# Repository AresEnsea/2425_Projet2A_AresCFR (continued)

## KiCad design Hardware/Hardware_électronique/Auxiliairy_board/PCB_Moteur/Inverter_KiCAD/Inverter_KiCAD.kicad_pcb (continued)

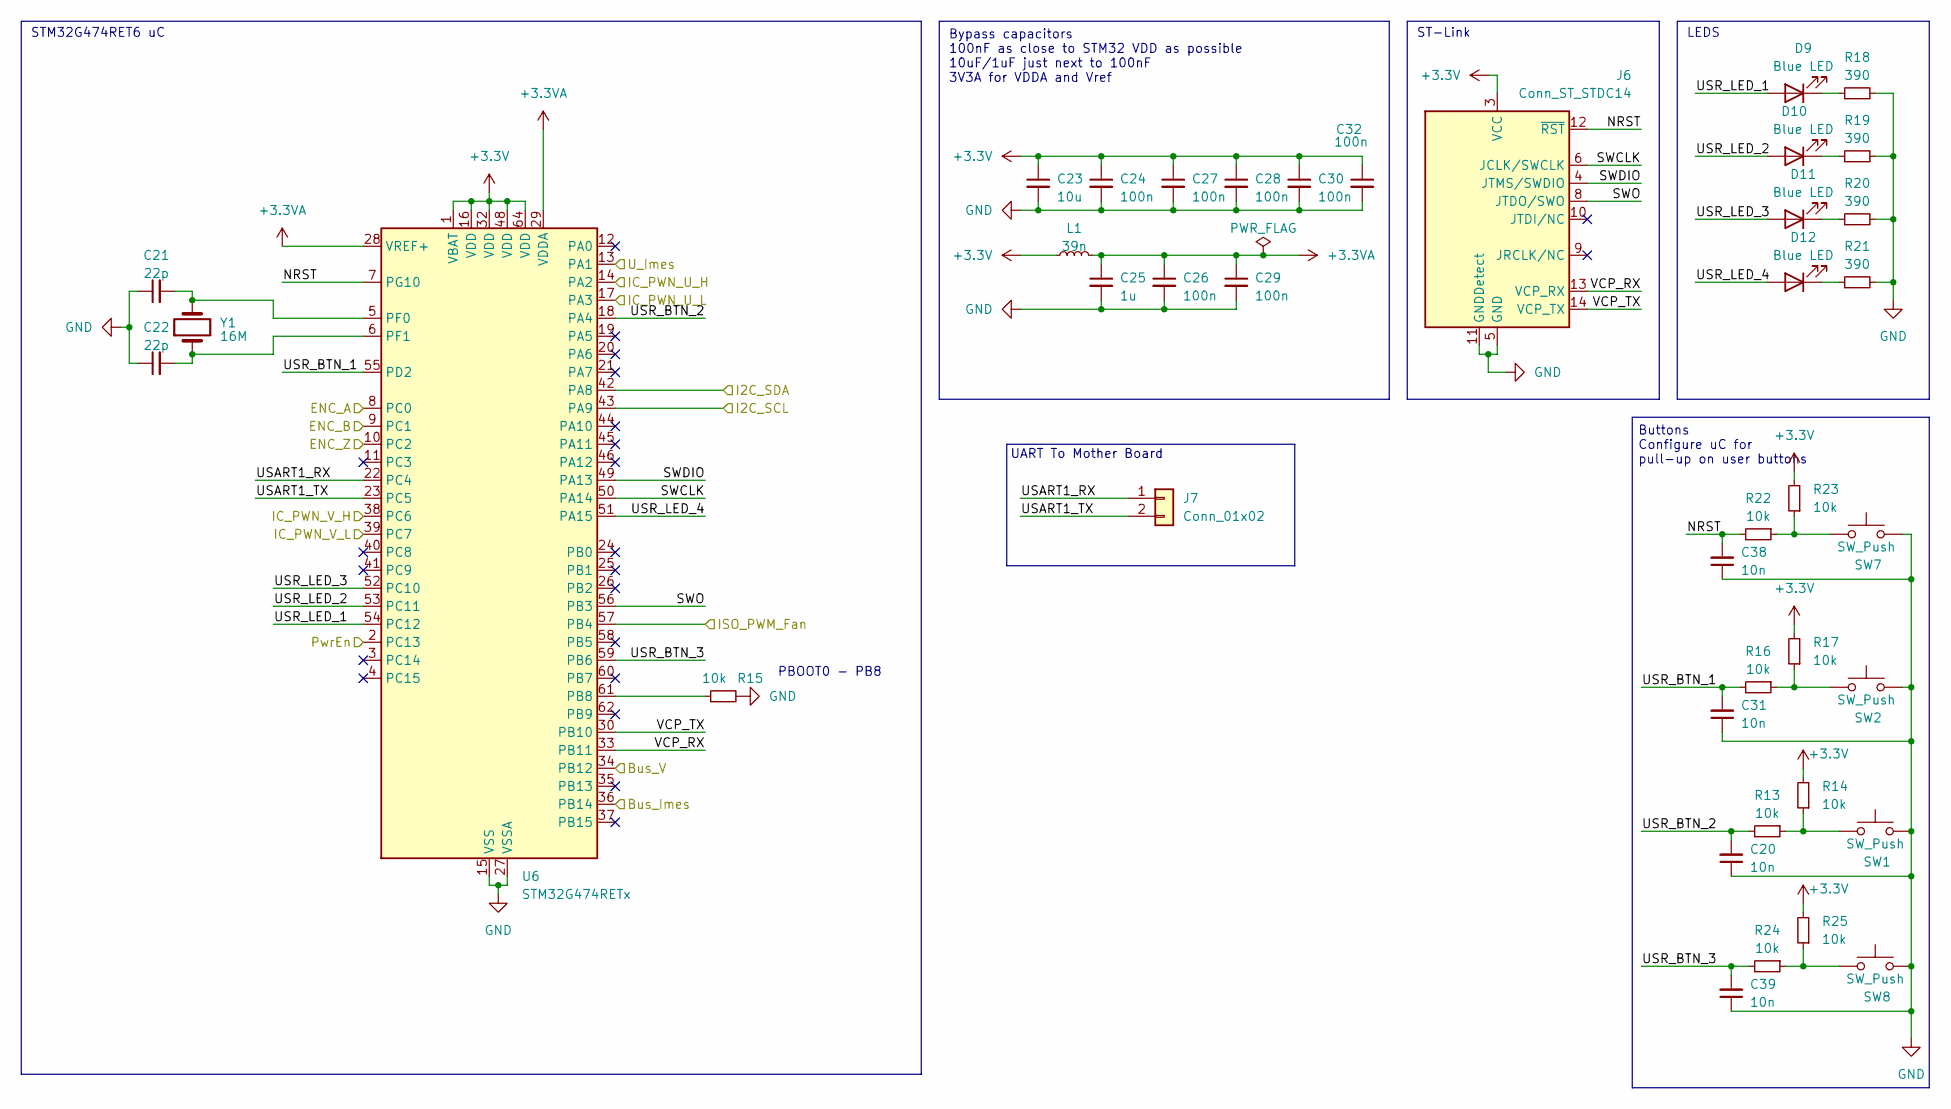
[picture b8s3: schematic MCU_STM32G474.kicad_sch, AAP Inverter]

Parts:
C20, C31, C38, C39: 10n; C_0402_1005Metric
C21, C22: 22p; C_0402_1005Metric
C23: 10u; C_0603_1608Metric_Pad1.08x0.95mm_HandSolder
C24, C26, C27, C28, C29, C30, C32: 100n; C_0402_1005Metric
C25: 1u; C_0603_1608Metric_Pad1.08x0.95mm_HandSolder
D9, D10, D11, D12: Blue LED; LED_0603_1608Metric
J6: Conn_ST_STDC14; PinHeader_2x07_P1.27mm_Vertical_SMD
J7: Conn_01x02; JST_XH_B2B-XH-A_1x02_P2.50mm_Vertical
L1: 39n; L_0603_1608Metric
R13, R14, R15, R16, R17, R22, R23, R24, R25: 10k; R_0402_1005Metric
R18, R19, R20, R21: 390; R_0402_1005Metric
SW1, SW2, SW7, SW8: SW_Push; 435451019820
U6: STM32G474RETx; LQFP-64_10x10mm_P0.5mm
Y1: 16M; ABLS-7.3728MHZ-CL-RESR-A-1-G-F

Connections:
+3.3V: C23.1, C24.1, C27.1, C28.1, C30.1, C32.1, J6.3 (VCC), L1.1, R14.2, R17.2, R23.2, R25.2, U6.1 (VBAT), U6.16 (VDD), U6.32 (VDD), U6.48 (VDD), U6.64 (VDD); also elsewhere on the board
+3.3VA: C25.1, C26.1, C29.1, L1.2, U6.28 (VREF+), U6.29 (VDDA)
/ENC_A: U6.8 (PC0); also elsewhere on the board
/ENC_B: U6.9 (PC1); also elsewhere on the board
/ENC_C: U6.10 (PC2); also elsewhere on the board
/I2C_SCL: U6.43 (PA9); also elsewhere on the board
/I2C_SDA: U6.42 (PA8); also elsewhere on the board
/Imes_mot: U6.13 (PA1); also elsewhere on the board
/Imes_vbus: U6.36 (PB14); also elsewhere on the board
/In_A_H: U6.14 (PA2); also elsewhere on the board
/In_A_L: U6.17 (PA3); also elsewhere on the board
/In_B_H: U6.38 (PC6); also elsewhere on the board
/In_B_L: U6.39 (PC7); also elsewhere on the board
/MCU_STM32G475/NRST: C38.2, J6.12 (~RST), R22.2, U6.7 (PG10)
/MCU_STM32G475/SWCLK: J6.6 (JCLK/SWCLK), U6.50 (PA14)
/MCU_STM32G475/SWDIO: J6.4 (JTMS/SWDIO), U6.49 (PA13)
/MCU_STM32G475/SWO: J6.8 (JTDO/SWO), U6.56 (PB3)
/MCU_STM32G475/USR_BTN_1: C31.2, R16.2, U6.55 (PD2)
/MCU_STM32G475/USR_BTN_2: C20.2, R13.2, U6.18 (PA4)
/MCU_STM32G475/USR_BTN_3: C39.2, R24.2, U6.59 (PB6)
/MCU_STM32G475/USR_LED_1: D9.2 (A), U6.54 (PC12)
/MCU_STM32G475/USR_LED_2: D10.2 (A), U6.53 (PC11)
/MCU_STM32G475/USR_LED_3: D11.2 (A), U6.52 (PC10)
/MCU_STM32G475/USR_LED_4: D12.2 (A), U6.51 (PA15)
/MCU_STM32G475/VCP_RX: J6.13 (VCP_RX), U6.33 (PB11)
/MCU_STM32G475/VCP_TX: J6.14 (VCP_TX), U6.30 (PB10)
/PWM_FAN: U6.57 (PB4); also elsewhere on the board
/Pwr_EN: U6.2 (PC13); also elsewhere on the board
/VBus_Sense: U6.34 (PB12); also elsewhere on the board
GND: C20.1, C21.1, C22.1, C23.2, C24.2, C25.2, C26.2, C27.2, C28.2, C29.2, C30.2, C31.1, C32.2, C38.1, C39.1, J6.5 (GND), J6.7 (GND), J6.11 (GNDDetect), J7.4, R15.2, R18.2, R19.2, R20.2, R21.2, SW1.2, SW2.2, SW7.2, SW8.2, U6.15 (VSS), U6.27 (VSSA), U6.31 (VSS), U6.47 (VSS), U6.63 (VSS); also elsewhere on the board
unnamed: D9.1 (K), R18.1
unnamed: D10.1 (K), R19.1
unnamed: D11.1 (K), R20.1
unnamed: D12.1 (K), R21.1
unnamed: R13.1, R14.1, SW1.1
unnamed: R16.1, R17.1, SW2.1
unnamed: R22.1, R23.1, SW7.1
unnamed: R24.1, R25.1, SW8.1
unnamed: R15.1, U6.61 (PB8)
unnamed: C21.2, U6.5 (PF0), Y1.2
unnamed: C22.2, U6.6 (PF1), Y1.1

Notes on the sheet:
ST-Link
Bypass capacitors 100nF as close to STM32 VDD as possible 10uF/1uF just next to 100nF 3V3A for VDDA and Vref
Buttons Configure uC for pull-up on user buttons
UART To Mother Board
PBOOT0 - PB8
STM32G474RET6 uC
LEDS

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
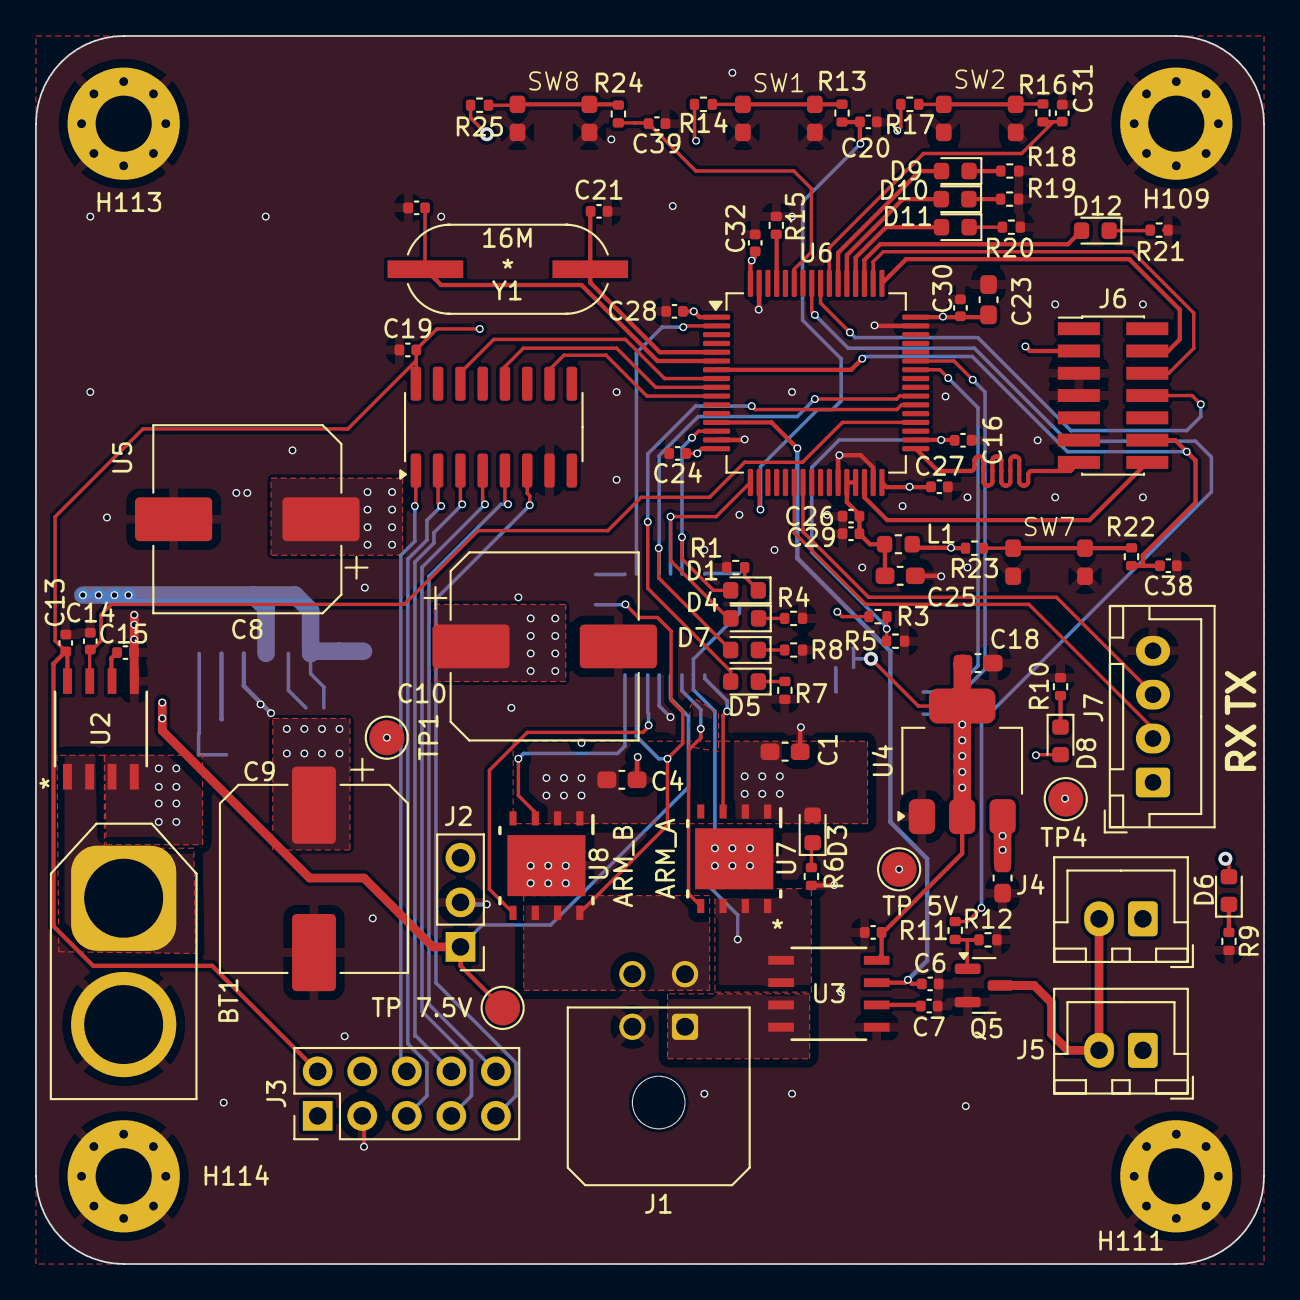
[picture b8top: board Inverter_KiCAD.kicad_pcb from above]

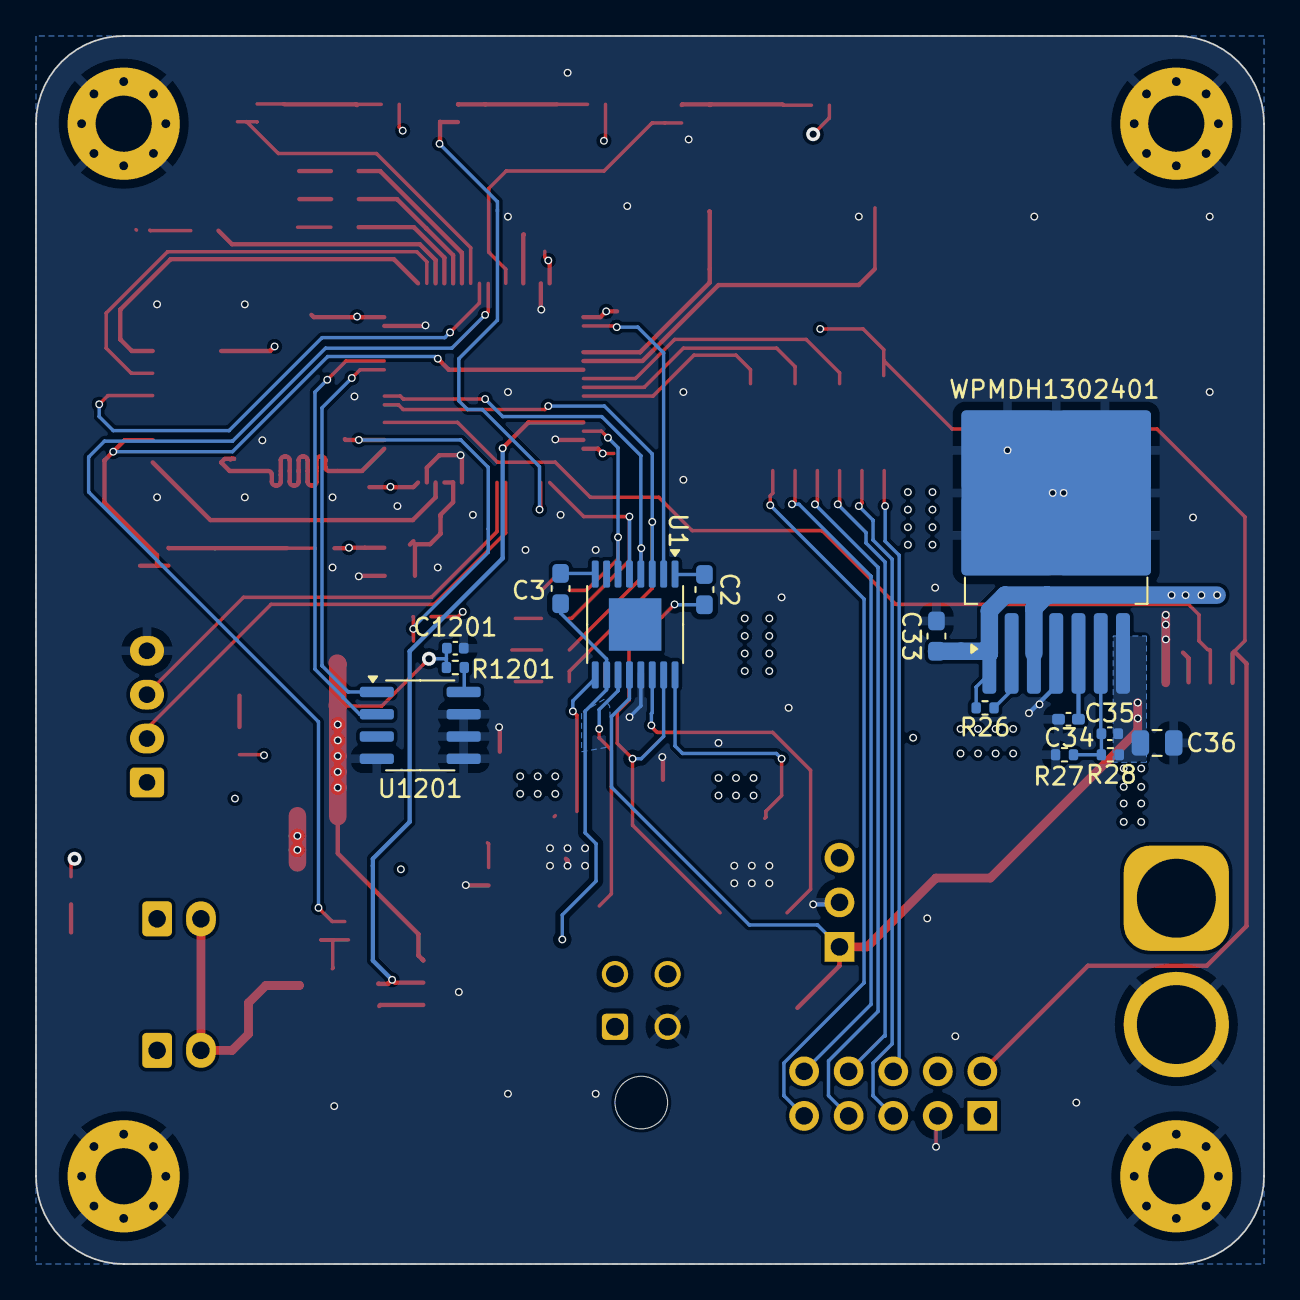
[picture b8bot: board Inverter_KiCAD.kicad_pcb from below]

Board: 4 copper layers, 70.0 x 70.0 mm, 109 parts (14 on the bottom side), 77 nets.

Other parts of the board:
TP 5V, TP 7.5V: TestPoint; TestPoint_Pad_D2.0mm
WPMDH1302401: TO-263-7_TabPin8

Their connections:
+5V: TP 5V.1; also elsewhere on the board
+7.5V: TP 7.5V.1, WPMDH1302401.7 (Vout); also elsewhere on the board
GND: WPMDH1302401.4 (AGND), WPMDH1302401.8 (PGND); also elsewhere on the board
unnamed 48: WPMDH1302401.6 (FB); also elsewhere on the board
unnamed 49: WPMDH1302401.2 (RON); also elsewhere on the board
unnamed 50: WPMDH1302401.5 (SS); also elsewhere on the board
VBUS: WPMDH1302401.1 (Vin), WPMDH1302401.3 (EN); also elsewhere on the board

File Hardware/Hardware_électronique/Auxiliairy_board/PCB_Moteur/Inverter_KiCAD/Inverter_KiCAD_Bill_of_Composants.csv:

Reference;Value;Datasheet;Footprint;Qty;Magasin
BT1;Battery;~;Connector_AMASS:AMASS_XT60-M_1x02_P7.20mm_Vertical;1;
C1,C4,C17,C23,C33;10u;-- valeurs mixtées --;Capacitor_SMD:C_0603_1608Metric_Pad1.08x0.95mm_HandSolder;5;
C2,C3,C25;1u;~;Capacitor_SMD:C_0603_1608Metric_Pad1.08x0.95mm_HandSolder;3;
C5,C6,C7,C13,C14,C15;4.7n;~;Capacitor_SMD:C_0402_1005Metric;6;
C8,C9,C10;220u;~;Capacitor_SMD:CP_Elec_10x10.5;3;
C16,C20,C31,C38,C39;10n;~;Capacitor_SMD:C_0402_1005Metric;5;
C18;22u;~;Capacitor_SMD:C_0603_1608Metric_Pad1.08x0.95mm_HandSolder;1;
C19,C24,C26,C27,C28,C29,C30,C32,C1201;100n;~;Capacitor_SMD:C_0402_1005Metric;9;
C21,C22;22p;~;Capacitor_SMD:C_0402_1005Metric;2;
C34;4.7nF;~;Capacitor_SMD:C_0402_1005Metric_Pad0.74x0.62mm_HandSolder;1;
C35;22nF;~;Capacitor_SMD:C_0402_1005Metric;1;
C36;47u;~;Capacitor_SMD:C_0805_2012Metric;1;
Converter_DCDC_WPMDH1302401;~;;Package_TO_SOT_SMD:TO-263-7_TabPin8;1;
D1,D3,D4,D5,D6,D7,D8;Red LED;~;LED_SMD:LED_0603_1608Metric;7;
D9,D10,D11,D12;Blue LED;~;LED_SMD:LED_0603_1608Metric;4;
H109,H111,H113,H114;MountingHole_Pad;~;MountingHole:MountingHole_3.2mm_M3_Pad_Via;4;
J1;Conn_02x02_Top_Bottom;~;Connector_Molex:Molex_Micro-Fit_3.0_43045-0400_2x02_P3.00mm_Horizontal;1;
J2;173010542;https://www.we-online.com/components/products/datasheet/1730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;Connector_PinHeader_2.54mm:PinHeader_1x03_P2.54mm_Vertical;1;
J3;Conn_02x05_Odd_Even;~;Connector_PinHeader_2.54mm:PinHeader_2x05_P2.54mm_Vertical;1;
J4,J5;Conn_01x02;~;Connector_JST:JST_XH_B2B-XH-A_1x02_P2.50mm_Vertical;2;
J6;Conn_ST_STDC14;https://www.st.com/content/ccc/resource/technical/document/u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;Connector_PinHeader_1.27mm:PinHeader_2x07_P1.27mm_Vertical_SMD;1;
J7;Conn_01x04_Pin;~;Connector_JST:JST_XH_B4B-XH-A_1x04_P2.50mm_Vertical;1;
L1;39n;~;Inductor_SMD:L_0603_1608Metric;1;
Q5;SQ2310ES;~;Package_TO_SOT_SMD:SOT-23;1;
R1,R4,R7,R8,R10,R18,R19,R20,R21;390;~;Resistor_SMD:R_0402_1005Metric;9;
R3;100k;~;Resistor_SMD:R_0402_1005Metric;1;
R5;8.2K;~;Resistor_SMD:R_0402_1005Metric;1;
R6;2k7;~;Resistor_SMD:R_0402_1005Metric;1;
R9;680;~;Resistor_SMD:R_0402_1005Metric;1;
R11;22;~;Resistor_SMD:R_0402_1005Metric;1;
R12,R13,R14,R15,R16,R17,R22,R23,R24,R25;10k;~;Resistor_SMD:R_0402_1005Metric;10;
R26;287k;~;Resistor_SMD:R_0402_1005Metric;1;
R27;1.91k;~;Resistor_SMD:R_0402_1005Metric;1;
R28;34k;~;Resistor_SMD:R_0402_1005Metric;1;
R1201;200;~;Resistor_SMD:R_0402_1005Metric;1;
SW1,SW2,SW7,SW8;SW_Push;~;Custom:435451019820;4;
TP1,TP2,TP3,TP4;TestPoint;~;TestPoint:TestPoint_Pad_D2.0mm;4;
U1;MIC4606;https://www.mouser.fr/datasheet/2/268/MIC4606_85V_Full_Bridg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;Package_SO:TSSOP-16-1EP_4.4x5mm_P0.65mm_EP3x3mm;1;
U2,U3;GO 10-SME/SP3;GO 10-SME;Custom:SOIC8-GO-SME&slash_SP3_LEM;2;
U4;AZ1117-3.3;https://www.diodes.com/assets/Datasheets/AZ1117.pdf;Package_TO_SOT_SMD:SOT-223-3_TabPin2;1;
U5;MAX3097ECSE+;https://www.mouser.fr/datasheet/2/609/MAX3097E_MAX3098E-3128450.pdf;Package_SO:SOIC-16_3.9x9.9mm_P1.27mm;1;
U6;STM32G474RETx;https://www.st.com/resource/en/datasheet/stm32g474re.pdf;Package_QFP:LQFP-64_10x10mm_P0.5mm;1;
U7,U8;CSD86350Q5D;CSD86350Q5D;CSD87351Q5D:DQY0008A;2;
U1201;TCN75A;https://docs.rs-online.com/fc92/0900766b80d0dfb5.pdf;Package_SO:SOIC-8_3.9x4.9mm_P1.27mm;1;
Y1;16M;https://4donline.ihs.com/images/VipMasterIC/IC/ABRC/ABRCS034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;Custom:ABLS-7.3728MHZ-CL-RESR-A-1-G-F;1;

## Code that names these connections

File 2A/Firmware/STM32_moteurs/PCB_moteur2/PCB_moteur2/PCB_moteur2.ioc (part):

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Mcu.Name=STM32G474R(B-C-E)Tx
Mcu.Package=LQFP64
Mcu.UserName=STM32G474RETx
PA1.Mode=IN2-Single-Ended
PA1.Signal=ADC1_IN2
PA13.Mode=Trace_Asynchronous_SW
PA13.Signal=SYS_JTMS-SWDIO
PA14.Mode=Trace_Asynchronous_SW
PA14.Signal=SYS_JTCK-SWCLK
PA15.GPIOParameters=GPIO_Label
PA15.GPIO_Label=USR_LED_4
PA15.Signal=GPIO_Output
PA2.Signal=S_TIM2_CH3
PA3.Signal=S_TIM2_CH4
PA4.GPIOParameters=GPIO_Label
PA4.GPIO_Label=USR_BTN_2
PA4.Signal=GPXTI4
PA8.Mode=I2C
PA8.Signal=I2C2_SDA
PA9.Mode=I2C
PA9.Signal=I2C2_SCL
PB10.GPIOParameters=GPIO_Label
PB10.GPIO_Label=VCP_TX
PB10.Mode=Asynchronous
PB10.Signal=USART3_TX
PB11.GPIOParameters=GPIO_Label
PB11.GPIO_Label=VCP_RX
PB11.Mode=Asynchronous
PB11.Signal=USART3_RX
PB12.GPIOParameters=GPIO_Label
PB12.GPIO_Label=BUS_V
PB12.Mode=IN11-Single-Ended
PB12.Signal=ADC1_IN11
PB14.GPIOParameters=GPIO_Label
PB14.GPIO_Label=BUS_Imes
PB14.Mode=IN5-Single-Ended
PB14.Signal=ADC1_IN5
PB3.Mode=Trace_Asynchronous_SW
PB3.Signal=SYS_JTDO-SWO
PB4.Signal=S_TIM16_CH1
PB6.GPIOParameters=GPIO_Label
PB6.GPIO_Label=USR_BTN_3
PB6.Signal=GPXTI6
PC0.GPIOParameters=GPIO_Label
PC0.GPIO_Label=ENC_A
PC0.Signal=S_TIM1_CH1
PC1.GPIOParameters=GPIO_Label
PC1.GPIO_Label=ENC_B
PC1.Signal=S_TIM1_CH2
PC10.GPIOParameters=GPIO_Label
PC10.GPIO_Label=USR_LED_3
PC10.Signal=GPIO_Output
PC11.GPIOParameters=GPIO_Label
PC11.GPIO_Label=USR_LED_2
PC11.Signal=GPIO_Output
PC12.GPIOParameters=GPIO_Label
PC12.GPIO_Label=USR_LED_1
PC12.Signal=GPIO_Output
PC13.GPIOParameters=GPIO_Label
PC13.GPIO_Label=MOTOR_EN
PC13.Signal=GPIO_Output
PC2.GPIOParameters=GPIO_Label
PC2.GPIO_Label=ENC_Z
PC2.Signal=GPIO_Input
PC4.GPIOParameters=GPIO_Label
PC4.GPIO_Label=CMD_TX
PC4.Mode=Asynchronous
PC4.Signal=USART1_TX
PC5.GPIOParameters=GPIO_Label
PC5.GPIO_Label=CMD_RX
PC5.Mode=Asynchronous
PC5.Signal=USART1_RX
PC6.Signal=S_TIM3_CH1
PC7.Signal=S_TIM3_CH2
PD2.GPIOParameters=GPIO_Label
PD2.GPIO_Label=USR_BTN_1
PD2.Signal=GPXTI2
PF0-OSC_IN.Mode=HSE-External-Oscillator
PF0-OSC_IN.Signal=RCC_OSC_IN
PF1-OSC_OUT.Mode=HSE-External-Oscillator
PF1-OSC_OUT.Signal=RCC_OSC_OUT
RCC.HSE_VALUE=16000000
RCC.SYSCLKFreq_VALUE=160000000
RCC.SYSCLKSource=RCC_SYSCLKSOURCE_PLLCLK
board=custom

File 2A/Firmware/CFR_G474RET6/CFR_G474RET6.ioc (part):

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Mcu.Name=STM32G474R(B-C-E)Tx
Mcu.Package=LQFP64
Mcu.UserName=STM32G474RETx
PA1.GPIOParameters=GPIO_Label
PA1.GPIO_Label=U_Imes
PA1.Mode=IN2-Differential
PA1.Signal=ADC1_IN2
PA11.Mode=Device
PA11.Signal=USB_DM
PA12.Mode=Device
PA12.Signal=USB_DP
PA13.GPIOParameters=GPIO_Label
PA13.GPIO_Label=SWDIO
PA13.Signal=SYS_JTMS-SWDIO
PA14.GPIOParameters=GPIO_Label
PA14.GPIO_Label=SWCLK
PA14.Signal=SYS_JTCK-SWCLK
PA15.GPIOParameters=GPIO_Label
PA15.GPIO_Label=USR_LED_4
PA15.Signal=GPIO_Output
PA2.GPIOParameters=GPIO_Label
PA2.GPIO_Label=IC_PWM_U_H
PA2.Mode=IN2-Differential
PA2.Signal=ADC1_IN3
PA3.GPIOParameters=GPIO_Label
PA3.GPIO_Label=IC_PWM_U_L
PA3.Mode=IN4-Differential
PA3.Signal=ADC1_IN4
PA4.GPIOParameters=GPIO_Label
PA4.GPIO_Label=USR_BTN_2
PA4.Signal=GPIO_Input
PA8.Signal=I2C2_SDA
PA9.Signal=I2C2_SCL
PB10.GPIOParameters=GPIO_Label
PB10.GPIO_Label=VCP_RX
PB10.Signal=LPUART1_RX
PB11.GPIOParameters=GPIO_Label
PB11.GPIO_Label=VCP_TX
PB11.Signal=LPUART1_TX
PB12.Signal=ADC4_IN3
PB14.Mode=IN4-Differential
PB14.Signal=ADC1_IN5
PB3.GPIOParameters=GPIO_Label
PB3.GPIO_Label=SWO
PB3.Signal=SYS_JTDO-SWO
PB4.GPIOParameters=GPIO_Label
PB4.GPIO_Label=ISO_PWM_Fan
PB4.Signal=S_TIM3_CH1
PB6.GPIOParameters=GPIO_Label
PB6.GPIO_Label=USR_BTN_3
PB6.Signal=GPIO_Output
PC1.GPIOParameters=GPIO_Label
PC1.GPIO_Label=ENC_A
PC1.Mode=IN7-Differential
PC1.Signal=ADC1_IN7
PC10.GPIOParameters=GPIO_Label
PC10.GPIO_Label=USR_LED_3
PC10.Signal=GPIO_Output
PC11.GPIOParameters=GPIO_Label
PC11.GPIO_Label=USR_LED_2
PC11.Signal=GPIO_Output
PC12.GPIOParameters=GPIO_Label
PC12.GPIO_Label=USR_LED_1
PC12.Signal=GPIO_Output
PC13.GPIOParameters=GPIO_Label
PC13.GPIO_Label=PwrEn
PC13.Signal=GPIO_Output
PC2.GPIOParameters=GPIO_Label
PC2.GPIO_Label=ENC_B
PC2.Mode=IN7-Differential
PC2.Signal=ADC1_IN8
PC3.GPIOParameters=GPIO_Label
PC3.GPIO_Label=ENC_Z
PC3.Signal=ADC1_IN9
PC4.Mode=Asynchronous
PC4.Signal=USART1_TX
PC5.Mode=Asynchronous
PC5.Signal=USART1_RX
PC7.GPIOParameters=GPIO_Label
PC7.GPIO_Label=IC_PWM_V_L
PC7.Signal=S_TIM3_CH2
PD2.GPIOParameters=GPIO_Label
PD2.GPIO_Label=USR_BTN_1
PD2.Signal=GPIO_Input
RCC.HSE_VALUE=8000000
RCC.SYSCLKFreq_VALUE=16000000
board=custom

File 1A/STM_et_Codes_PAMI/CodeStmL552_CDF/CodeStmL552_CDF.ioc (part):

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Mcu.Name=STM32L552C(C-E)Tx
Mcu.Package=LQFP48
Mcu.UserName=STM32L552CCTx
PA13\ (JTMS/SWDIO).Mode=Trace_Asynchronous_SW
PA13\ (JTMS/SWDIO).Signal=DEBUG_JTMS-SWDIO
PA14\ (JTCK/SWCLK).Mode=Trace_Asynchronous_SW
PA14\ (JTCK/SWCLK).Signal=DEBUG_JTCK-SWCLK
PA2.Mode=Asynchronous
PA2.Signal=USART2_TX
PA3.Mode=Asynchronous
PA3.Signal=USART2_RX
PA4.GPIOParameters=GPIO_Label
PA4.GPIO_Label=X1
PA4.Signal=ADCx_IN9
PA5.GPIOParameters=GPIO_Label
PA5.GPIO_Label=X2
PA5.Signal=ADCx_IN10
PA6.GPIOParameters=GPIO_Label
PA6.GPIO_Label=X3
PA6.Signal=ADCx_IN11
PA7.GPIOParameters=GPIO_Label
PA7.GPIO_Label=X4
PA7.Signal=ADCx_IN12
PA8.GPIOParameters=GPIO_Label
PA8.GPIO_Label=Servo2
PA8.Signal=S_TIM1_CH1
PA9.GPIOParameters=GPIO_Label
PA9.GPIO_Label=Servo1
PA9.Signal=S_TIM1_CH2
PB0.GPIOParameters=GPIO_PuPd,GPIO_Label,GPIO_ModeDefaultEXTI
PB0.GPIO_Label=Button
PB0.GPIO_ModeDefaultEXTI=GPIO_MODE_IT_RISING
PB0.GPIO_PuPd=GPIO_NOPULL
PB0.Signal=GPXTI0
PB12.GPIOParameters=GPIO_Label
PB12.GPIO_Label=TRIG
PB12.Signal=GPIO_Output
PB13.GPIOParameters=GPIO_Label,GPIO_ModeDefaultEXTI
PB13.GPIO_Label=ECHO
PB13.GPIO_ModeDefaultEXTI=GPIO_MODE_IT_RISING_FALLING
PB13.Signal=GPXTI13
PB3\ (JTDO/TRACESWO).Mode=Trace_Asynchronous_SW
PB3\ (JTDO/TRACESWO).Signal=DEBUG_JTDO-SWO
PB4\ (NJTRST).GPIOParameters=GPIO_Label
PB4\ (NJTRST).GPIO_Label=AIN2
PB4\ (NJTRST).Signal=GPIO_Output
PB5.GPIOParameters=GPIO_Label
PB5.GPIO_Label=AIN1
PB5.Signal=GPIO_Output
PB6.GPIOParameters=GPIO_Label
PB6.GPIO_Label=PWMA
PB6.Signal=S_TIM4_CH1
PB7.GPIOParameters=GPIO_Label
PB7.GPIO_Label=STBY
PB7.Signal=GPIO_Output
PB8.GPIOParameters=GPIO_Label
PB8.GPIO_Label=BIN2
PB8.Signal=GPIO_Output
PB9.GPIOParameters=GPIO_Label
PB9.GPIO_Label=PWMB
PB9.Signal=S_TIM4_CH4
PH0-OSC_IN\ (PH0).Mode=HSE-External-Oscillator
PH0-OSC_IN\ (PH0).Signal=RCC_OSC_IN
PH1-OSC_OUT\ (PH1).Mode=HSE-External-Oscillator
PH1-OSC_OUT\ (PH1).Signal=RCC_OSC_OUT
PH3-BOOT0.GPIOParameters=GPIO_Label
PH3-BOOT0.GPIO_Label=BIN1
PH3-BOOT0.Signal=GPIO_Output
RCC.HSE_VALUE=16000000
RCC.SYSCLKFreq_VALUE=80000000
RCC.SYSCLKSource=RCC_SYSCLKSOURCE_PLLCLK
board=custom

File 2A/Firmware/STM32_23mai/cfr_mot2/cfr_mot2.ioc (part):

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Mcu.Name=STM32L476R(C-E-G)Tx
Mcu.Package=LQFP64
Mcu.UserName=STM32L476RGTx
PA0.Mode=Asynchronous
PA0.Signal=UART4_TX
PA1.Mode=Asynchronous
PA1.Signal=UART4_RX
PA10.Signal=S_TIM1_CH3
PA13\ (JTMS-SWDIO).GPIOParameters=GPIO_Label
PA13\ (JTMS-SWDIO).GPIO_Label=TMS
PA13\ (JTMS-SWDIO).Mode=Serial_Wire
PA13\ (JTMS-SWDIO).Signal=SYS_JTMS-SWDIO
PA14\ (JTCK-SWCLK).GPIOParameters=GPIO_Label
PA14\ (JTCK-SWCLK).GPIO_Label=TCK
PA14\ (JTCK-SWCLK).Mode=Serial_Wire
PA14\ (JTCK-SWCLK).Signal=SYS_JTCK-SWCLK
PA2.Mode=Asynchronous
PA2.Signal=USART2_TX
PA3.GPIOParameters=GPIO_Speed,GPIO_PuPd,GPIO_Label,GPIO_Mode
PA3.GPIO_Label=USART_RX
PA3.GPIO_Mode=GPIO_MODE_AF_PP
PA3.GPIO_PuPd=GPIO_NOPULL
PA3.GPIO_Speed=GPIO_SPEED_FREQ_VERY_HIGH
PA3.Mode=Asynchronous
PA3.Signal=USART2_RX
PA5.GPIOParameters=GPIO_Speed,GPIO_PuPd,GPIO_Label,GPIO_ModeDefaultOutputPP
PA5.GPIO_Label=LD2 [green Led]
PA5.GPIO_ModeDefaultOutputPP=GPIO_MODE_OUTPUT_PP
PA5.GPIO_PuPd=GPIO_NOPULL
PA5.GPIO_Speed=GPIO_SPEED_FREQ_LOW
PA5.Signal=GPIO_Output
PA9.Signal=S_TIM1_CH2
PB10.Signal=S_TIM2_CH3
PB11.Signal=S_TIM2_CH4
PB4\ (NJTRST).Signal=GPIO_Output
PB5.Signal=GPIO_Output
PB6.Mode=Asynchronous
PB6.Signal=USART1_TX
PB7.Mode=Asynchronous
PB7.Signal=USART1_RX
PB8.Signal=GPIO_Output
PB9.Signal=GPIO_Output
PC0.Mode=Asynchronous
PC0.Signal=LPUART1_RX
PC1.Mode=Asynchronous
PC1.Signal=LPUART1_TX
PC13.GPIOParameters=GPIO_PuPd,GPIO_Label,GPIO_ModeDefaultEXTI
PC13.GPIO_Label=B1 [Blue PushButton]
PC13.GPIO_ModeDefaultEXTI=GPIO_MODE_IT_FALLING
PC13.GPIO_PuPd=GPIO_NOPULL
PC13.Signal=GPXTI13
PC14-OSC32_IN\ (PC14).Mode=LSE-External-Oscillator
PC14-OSC32_IN\ (PC14).Signal=RCC_OSC32_IN
PC15-OSC32_OUT\ (PC15).Mode=LSE-External-Oscillator
PC15-OSC32_OUT\ (PC15).Signal=RCC_OSC32_OUT
PC4.Mode=Asynchronous
PC4.Signal=USART3_TX
PC5.Mode=Asynchronous
PC5.Signal=USART3_RX
PH0-OSC_IN\ (PH0).Mode=HSE-External-Oscillator
PH0-OSC_IN\ (PH0).Signal=RCC_OSC_IN
PH1-OSC_OUT\ (PH1).Mode=HSE-External-Oscillator
PH1-OSC_OUT\ (PH1).Signal=RCC_OSC_OUT
RCC.HSE_VALUE=8000000
RCC.SYSCLKFreq_VALUE=80000000
RCC.SYSCLKSource=RCC_SYSCLKSOURCE_PLLCLK
board=NUCLEO-L476RG
boardIOC=true

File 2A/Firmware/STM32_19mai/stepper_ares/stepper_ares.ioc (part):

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Mcu.Name=STM32G071K(6-8-B)Ux
Mcu.Package=UFQFPN32
Mcu.UserName=STM32G071KBUx
PA10.GPIOParameters=GPIO_Label
PA10.GPIO_Label=step1
PA10.Signal=S_TIM1_CH3
PA2.Mode=Asynchronous
PA2.Signal=USART2_TX
PA3.Mode=Asynchronous
PA3.Signal=USART2_RX
PA4.GPIOParameters=GPIO_Label
PA4.GPIO_Label=dir2
PA4.Signal=GPIO_Output
PA5.GPIOParameters=GPIO_Label
PA5.GPIO_Label=EN2
PA5.Signal=GPIO_Output
PA6.GPIOParameters=GPIO_Label
PA6.GPIO_Label=step2
PA6.Signal=S_TIM3_CH1
PA9.GPIOParameters=GPIO_Label
PA9.GPIO_Label=dir1
PA9.Signal=GPIO_Output
PB6.Mode=Asynchronous
PB6.Signal=USART1_TX
PB7.Mode=Asynchronous
PB7.Signal=USART1_RX
PC14-OSC32_IN\ (PC14).Mode=LSE-External-Oscillator
PC14-OSC32_IN\ (PC14).Signal=RCC_OSC32_IN
PC15-OSC32_OUT\ (PC15).Mode=LSE-External-Oscillator
PC15-OSC32_OUT\ (PC15).Signal=RCC_OSC32_OUT
PC6.GPIOParameters=GPIO_Label
PC6.GPIO_Label=EN1
PC6.Signal=GPIO_Output
RCC.HSE_VALUE=8000000
RCC.SYSCLKFreq_VALUE=48000000
RCC.SYSCLKSource=RCC_SYSCLKSOURCE_PLLCLK
board=custom

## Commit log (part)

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2024-09-17 réarranger dossiers
2024-09-17 adding to hardware
2024-09-17 same
2024-09-19 Datasheet moteur choisi
2024-09-19 Datasheet reducteur choisi
2024-09-24 Creation du fichier demandes d'achats
2024-09-24 Rename Liens + Descriptions.mkd to Liens + Descriptions.md
2024-09-24 Rename Liens + Descriptions.md to README.md
2024-09-24 Datasheet billes achats
2024-09-24 Rename 166937_32mm_3Nm_213.36e.pdf to Reducteur_166937_32mm_3Nm_213.36e.pdf
2024-09-24 Rename A700000006810401.pdf to Billes_8883016_RS200-6385
2024-09-24 Datasheet codeur
2024-09-24 Rename 272768_40W_7220rpm_33,8mNm_258.89e_30mm.pdf to Moteur_Maxon_272768_40W_7220rpm_33,8mNm_258.89e_30mm.pdf
2024-09-24 Rename Capture d’écran du 2024-09-24 14-06-27.png to Roue_BaneBots_30A.png
2024-09-24 Rename Capture d’écran du 2024-09-24 13-59-06.png to T81_Hub_BaneBots
2024-09-24 Rename Capture d’écran du 2024-09-24 14-07-55.png to Roues_BaneBOts_40A
2024-09-24 Rename Codeur_Maxon_.pdf to Codeur_Maxon_.499361pdf
2024-09-25 Rename Craft_6_1_Introduction_to_ROS_Day1 - Presentation.webloc to Craft_6_1_Introduction_to_ROS_Day1 - Presentation.html
2024-09-25 Rename Craft_6_1_Introduction_to_ROS_Day1 - Presentation.html to Craft_6_1_Introduction_to_ROS_Day1 - Presentation.webloc
2024-09-26 simulation
2024-09-28 Ajout de cours de ROS provenant de l'ESIEE Paris
2024-09-28 Rename README to README.md
2024-09-30 fichiers STEP
2024-10-01 Adding motor board
2024-10-01 Rename Capture d'écran 2024-10-01 161902.png to Schéma élec global.png
2024-10-08 update schematic
2024-10-11 ros2_ws with serial package
2024-10-12 last schematic editing
    just miss a FB resistor value
2024-10-13 project stm32 for simple uart connexion with pi
2024-10-18 deut routage
2024-10-18 routage
2024-10-20 almost finished pcb
2024-10-21 G474 pinout
2024-10-21 finalization
    Rooting and last edits ready to go
2024-10-21 PCB motor oof
2024-10-22 moteurs and communication uart stm32 and pi
2024-10-22 hello
2024-10-22 Done !
2024-10-24 cfr_mot2
2024-10-24 cfr_moteurs qui fonctionne avec l'uart et la stm32
2024-11-04 correction workspace ros
2024-11-05 psst
2024-11-05 commitment
2024-11-12 approaching end of schematics
2024-11-13 quite finished schematics
2024-11-14 finished schematics missing footprints
2024-11-17 beginning of PCB design with Rpi4 shield shape
2024-11-18 Motherboard advance
2024-11-19 MotherBoard finished
2024-11-19 Mainboard Done !
2024-11-19 Stepper Board schematic begin
2024-11-20 Updating t
2024-11-20 Edits of the PCB done
2024-11-21 added 1A and 2A directories
2024-11-21 README 1A change
2024-11-21 Ajout du projet PAMI_F303K8 dans STM_et_Codes_PAMI
2024-11-21 Modif README CODES
2024-11-21 Ajout du projet Kicad PAMI 2425
2024-11-21 README modified
2024-11-25 update workspace ros
2024-11-26 base roulante code stm32
2024-11-28 added ir test
2024-11-30 test_ir
2024-12-02 Vision
2024-12-05 modif code main.c
2024-12-10 Equipe Vision
2024-12-10 last commit
2024-12-10 NIBA
2024-12-10 Commit ros2 pour pkg lidar. Merci au manager d'Ares, petit prince de Bretagne, soleil de l'ENSEA, empereur autoproclamé d'Ares, le British Napoleon pour sa décisivité dans ce commit et son assertivit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
2024-12-10 evolution of the stepper board
2024-12-17 add recovery for router1
2024-12-19 Ajout du dossier PAMI_4_IR_V0
2024-12-19 écran_strategie
2025-01-14 Create PCB_Servo
2025-01-14 Create PCB_Serevo
2025-01-15 workspace ros pour lidar
2025-01-20 Package lidar fonctionnel
2025-01-20 update reseau
2025-01-24 ajout safety_node lidar ros
2025-01-24 Mainboard v2
2025-01-24 modification README 1A
2025-01-24 Readme initialement sur un fork, reamenagement des fichiers
2025-01-24 Mauvais readme
2025-01-24 Update README.md
    base roulante
2025-01-24 Update README.md
    Bannière
2025-01-24 Update README.md
    Pinces élévatrices
2025-01-24 Update README.md
    Lien meca
2025-01-28 Centralisation du projet sur le workspace ros2_ws et intégration de la node qui permet aux moteurs de s'arrêter au signal du Lidar
2025-01-28 Correction PCB Servo LF
2025-01-28 Check Multiprise LF La grille PTN!
2025-01-28 last minute update
2025-01-28 recommit to be sure...
2025-01-29 change on kicad projects, remove errors
2025-01-30 Ajout launch lidar+serial avec arrêt, autrement dit robot homologable
2025-02-04 ajout du répertoire PCB_PAMI contenant la version finale du PCB
2025-02-07 ajout d'une node robot_control qui permet à l'utilisateur d'utiliser la pince
2025-02-10 Projet STM32 pour communication à 11 caractères (fonctionne avec la node robot_controle_node_3.py
2025-02-10 Mainboard v3
2025-02-12 PCB v3
2025-02-12 didn't save lol
2025-02-12 last details
2025-02-13 ajout de l'écran stm32 pour display les différents bags disponibles (dans le package serial node). Merci à Antoine Lemarignier pour son assertivité
2025-03-04 écran_stm
2025-03-04 correction en théorie
2025-03-12 Rename uart_class.cpp to UART_Node.cpp
2025-03-18 stm moteur
2025-03-18 stm32 code for fixing kenny's mistakes pcb output pwm
2025-03-20 ajout projet stm servo
2025-03-20 servo2.0
2025-03-20 update code
2025-03-28 stm mere
2025-03-31 update stm32
2025-03-31 pour lolo
2025-04-01 pcb edits
2025-04-01 stm32_mot_step
2025-04-02 carte_mere et stepper ok
2025-04-03 honore
2025-04-03 stepper fonctionel
2025-04-07 robot_node_control_6.py
2025-04-15 MAJ Code PAMI
2025-04-23 Version_Finale_Robot_Pose
2025-04-26 UpdateBackupNetworkBase
2025-04-26 Update README.md Réseau
2025-04-27 startup_file
2025-04-27 nouvelle_version_stm
2025-04-27 Update README.md
    Bannière vf
2025-04-27 Update README.md
    fixation pcb, antennes et routeur
2025-04-27 Update README.md
    Cable management
2025-04-27 Update README.md
    Tour vision
2025-04-27 Update README.md
    Correction d'erreurs
2025-04-28 last main board edis
2025-04-28 Last pcb edits for the motor board
2025-05-19 version_precoupe
2025-05-21 version_precoupe_21mai
2025-05-21 launch bag coupe
2025-05-23 version_23mai
2025-05-24 bag_playback (fusion du lanceur de bag et du bag listener avec démarrage écran tirette )
2025-05-24 version_24maiSTM
2025-05-26 stm26mai
2025-05-30 Create instructions_node
2025-05-30 Rename instructions_node to instructions_node.cpp
2025-05-30 Create instructions_jaune
2025-05-30 Create instructions_bleu
2025-05-30 Rename instructions_bleu to instructions_bleu.txt
2025-05-30 Rename instructions_jaune to instructions_jaune.txt
